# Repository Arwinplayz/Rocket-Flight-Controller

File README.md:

# Custom Flight Controller
A custom Flight Controller maded within kicad, specificaly for rockets.
---

## Project Overview
The goal was to create a custom Flight Controller which was capable of utilising TVC to guide a rocket.

---

## Screenshots

### 1. Overall

### 2. Schematic

### 3. PCB layout

### 4. Design

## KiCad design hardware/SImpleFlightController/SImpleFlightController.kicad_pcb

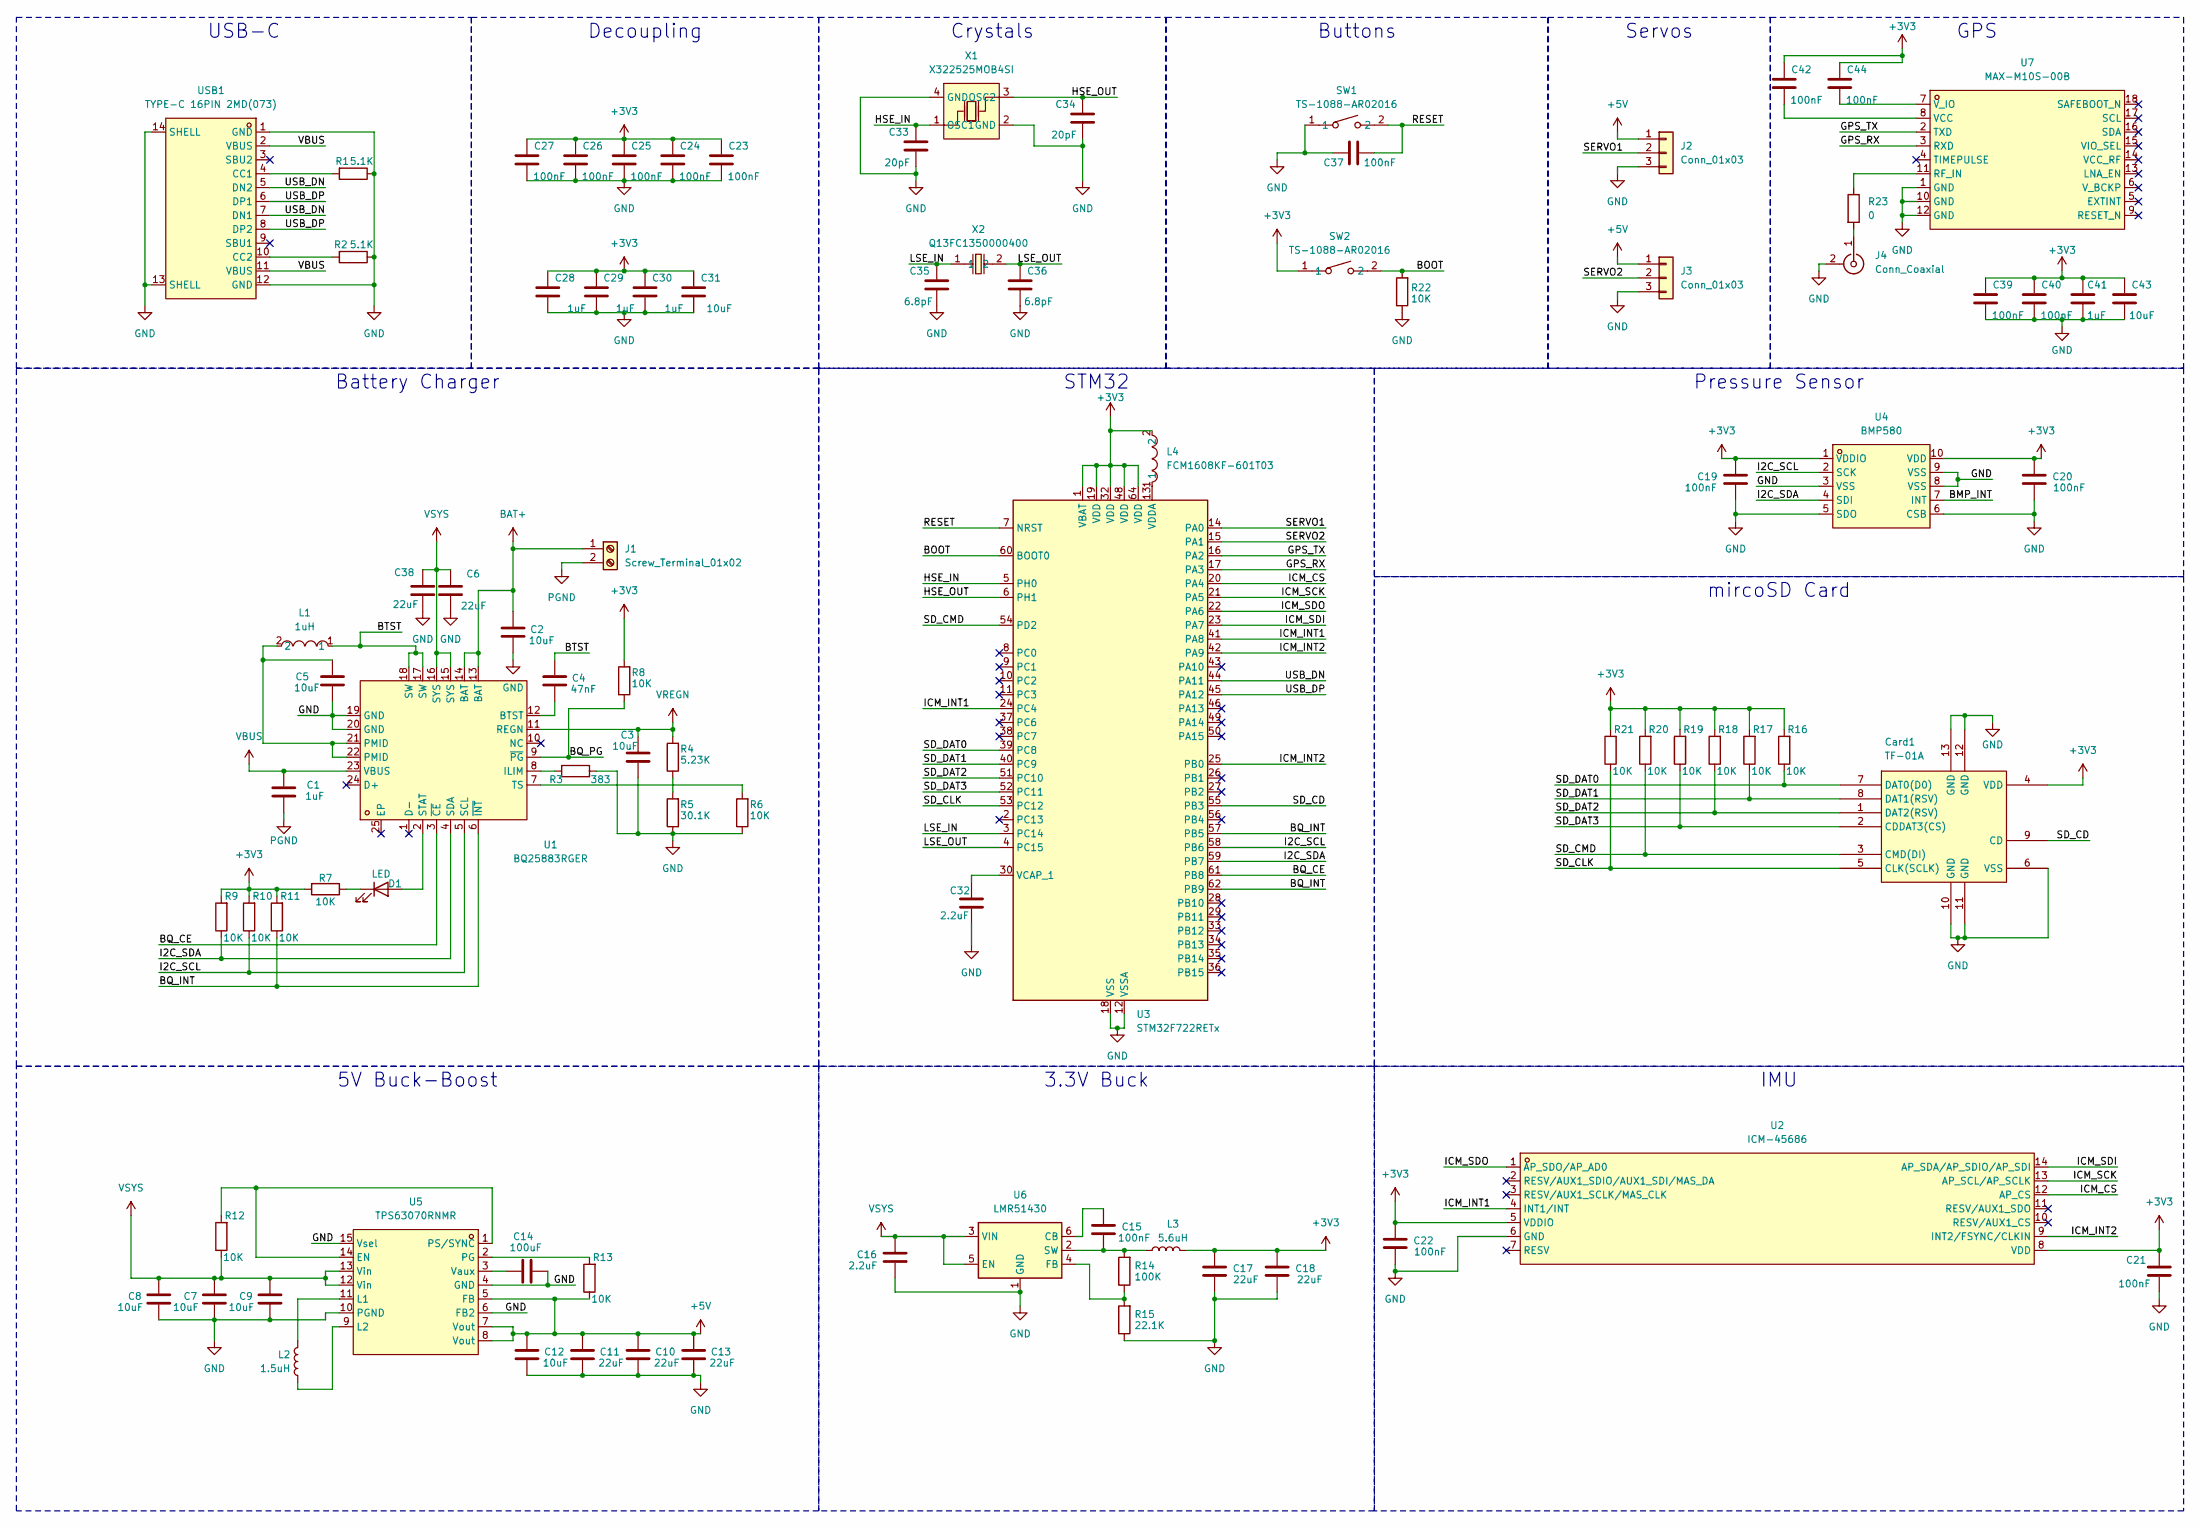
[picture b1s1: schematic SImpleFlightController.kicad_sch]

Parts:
C1, C28, C29, C30, C41: 1uF; C_0402_1005Metric
C2, C9, C12: 10uF; C_0603_1608Metric
C3, C5, C31, C43: 10uF; C_0402_1005Metric
C4: 47nF; C_0201_0603Metric
C6, C38: 22uF; C_0603_1608Metric
C7, C8: 10uF; C_0805_2012Metric
C10, C11, C13: 22uF; C_0805_2012Metric
C14: 100uF; C_0201_0603Metric
C15, C19, C20, C21, C22, C23, C24, C25, C26, C27, C37: 100nF; C_0201_0603Metric
C16: 2.2uF; C_0603_1608Metric
C17, C18: 22uF; C_0402_1005Metric
C32: 2.2uF; C_0201_0603Metric
C33, C34: 20pF; C_0201_0603Metric
C35, C36: 6.8pF; C_0201_0603Metric
C39, C40, C42, C44: 100nF; C_0402_1005Metric
Card1: TF-01A; TF-SMD_TF-01A; LCSC Part C91145
D1: LED; LED_0402_1005Metric
J1: Screw_Terminal_01x02; TerminalBlock_Xinya_XY308-2.54-2P_1x02_P2.54mm_Horizontal
J2, J3: Conn_01x03; PinHeader_1x03_P2.54mm_Vertical
J4: Conn_Coaxial; U.FL_Hirose_U.FL-R-SMT-1_Vertical
L1: 1uH; L2520; LCSC Part C435392
L2: 1.5uH; IND-SMD_L4.0-W4.0-A
L3: 5.6uH; IND-SMD_L3.0-W3.0
L4: FCM1608KF-601T03; L0603; LCSC Part C141723
R1, R2: 5.1K; R_0201_0603Metric
R3: 383; R_0201_0603Metric
R4: 5.23K; R_0201_0603Metric
R5: 30.1K; R_0201_0603Metric
R6, R7, R8, R9, R10, R11, R12, R13, R16, R17, R18, R19, R20, R21, R22: 10K; R_0201_0603Metric
R14: 100K; R_0402_1005Metric
R15: 22.1K; R_0402_1005Metric
R23: 0; R_0201_0603Metric
SW1, SW2: TS-1088-AR02016; SW-SMD_L3.9-W3.0-P4.45; LCSC Part C720477
U1: BQ25883RGER; VFQFPN-24_L4.0-W4.0-P0.50-BL-EP2.8; LCSC Part C544362
U2: ICM-45686; LGA-14_L3.0-W2.5-P0.50-TL; LCSC Part C22459454
U3: STM32F722RETx; LQFP-64_10x10mm_P0.5mm
U4: BMP580; LGA-10_L2.0-W2.0-P0.50-TL_BMP580; LCSC Part C22391138
U5: TPS63070RNMR; VQFN-HR-15_L3.0-W2.5-P0.50-BL_TPS63070RNMR; LCSC Part C109322
U6: LMR51430; SOT-23-6
U7: MAX-M10S-00B; SMD-18_L10.1-W9.7-P1.10-TL_SKG09F; LCSC Part C4153167
USB1: TYPE-C 16PIN 2MD(073); USB-C-SMD_TYPE-C-6PIN-2MD-073; LCSC Part C2765186
X1: X322525MOB4SI; CRYSTAL-SMD_4P-L3.2-W2.5-BL; LCSC Part C9006
X2: Q13FC1350000400; FC-135R_L3.2-W1.5; LCSC Part C32346

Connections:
+3V3: C17.1, C18.1, C19.1, C20.1, C21.1, C22.1, C23.1, C24.1, C25.1, C26.1, C27.1, C28.1, C29.1, C30.1, C31.1, C39.1, C40.1, C41.1, C42.1, C42.2, C43.1, C44.1, C44.2, Card1.4 (VDD), L3.2, L4.2, R7.2, R8.2, R9.2, R10.2, R11.2, R16.2, R17.2, R18.2, R19.2, R20.2, R21.2, SW2.1, U2.5 (VDDIO), U2.8 (VDD), U3.1 (VBAT), U3.19 (VDD), U3.32 (VDD), U3.48 (VDD), U3.64 (VDD), U4.1 (VDDIO), U4.10 (VDD), U7.7 (V_IO), U7.8 (VCC); also elsewhere on the board
+5V: C10.1, C11.1, C12.1, C13.1, J2.1, J3.1, R13.1, U5.5 (FB), U5.7 (Vout), U5.8 (Vout)
/BMP_INT: U4.7 (INT)
/BOOT: R22.2, SW2.2, U3.60 (BOOT0); also elsewhere on the board
/BQ_CE: U1.3 (~CE), U3.61 (PB8)
/BQ_INT: R11.1, U1.6 (~INT), U3.57 (PB5), U3.62 (PB9)
/BQ_PG: R8.1, U1.9 (~PG)
/BTST: C4.1, L1.1, U1.17 (SW), U1.18 (SW)
/GPS_RX: U3.17 (PA3), U7.3 (RXD)
/GPS_TX: U3.16 (PA2), U7.2 (TXD)
/HSE_IN: C33.1, U3.5 (PH0), X1.1 (OSC1)
/HSE_OUT: C34.1, U3.6 (PH1), X1.3 (OSC2)
/I2C_SCL: R10.1, U1.5 (SCL), U3.58 (PB6), U4.2 (SCK)
/I2C_SDA: R9.1, U1.4 (SDA), U3.59 (PB7), U4.4 (SDI)
/ICM_CS: U2.12 (AP_CS), U3.20 (PA4)
/ICM_INT1: U2.4 (INT1/INT), U3.24 (PC4), U3.41 (PA8)
/ICM_INT2: U2.9 (INT2/FSYNC/CLKIN), U3.25 (PB0), U3.42 (PA9)
/ICM_SCK: U2.13 (AP_SCL/AP_SCLK), U3.21 (PA5)
/ICM_SDI: U2.14 (AP_SDA/AP_SDIO/AP_SDI), U3.23 (PA7)
/ICM_SDO: U2.1 (AP_SDO/AP_AD0), U3.22 (PA6)
/LSE_IN: C35.1, U3.3 (PC14), X2.1
/LSE_OUT: C36.1, U3.4 (PC15), X2.2
/RESET: C37.2, SW1.2, U3.7 (NRST); also elsewhere on the board
/SD_CD: Card1.9 (CD), U3.55 (PB3)
/SD_CLK: Card1.5 (CLK(SCLK)), R21.1, U3.53 (PC12)
/SD_CMD: Card1.3 (CMD(DI)), R20.1, U3.54 (PD2)
/SD_DAT0: Card1.7 (DAT0(D0)), R16.1, U3.39 (PC8)
/SD_DAT1: Card1.8 (DAT1(RSV)), R17.1, U3.40 (PC9)
/SD_DAT2: Card1.1 (DAT2(RSV)), R18.1, U3.51 (PC10)
/SD_DAT3: Card1.2 (CDDAT3(CS)), R19.1, U3.52 (PC11)
/SERVO1: J2.2, U3.14 (PA0)
/SERVO2: J3.2, U3.15 (PA1)
/USB_DN: U3.44 (PA11), USB1.5 (DN2), USB1.7 (DN1)
/USB_DP: U3.45 (PA12), USB1.6 (DP1), USB1.8 (DP2)
BAT+: C2.1, J1.1, U1.13 (BAT), U1.14 (BAT)
GND: C2.2, C3.2, C5.2, C6.2, C7.2, C8.2, C9.2, C10.2, C11.2, C12.2, C13.2, C14.1, C16.2, C17.2, C18.2, C19.2, C20.2, C21.2, C22.2, C23.2, C24.2, C25.2, C26.2, C27.2, C28.2, C29.2, C30.2, C31.2, C32.2, C33.2, C34.2, C35.2, C36.2, C37.1, C38.2, C39.2, C40.2, C41.2, C43.2, Card1.6 (VSS), Card1.10 (GND), Card1.11 (GND), Card1.12 (GND), Card1.13 (GND), J2.3, J3.3, J4.2 (Ext), R1.1, R2.1, R3.1, R5.1, R6.1, R15.1, R22.1, SW1.1, U1.19 (GND), U1.20 (GND), U2.6 (GND), U3.12 (VSSA), U3.18 (VSS), U3.31 (VSS), U3.47 (VSS), U3.63 (VSS), U4.3 (VSS), U4.5 (SDO), U4.6 (CSB), U4.8 (VSS), U4.9 (VSS), U5.4 (GND), U5.6 (FB2), U5.10 (PGND), U5.15 (Vsel), U6.1 (GND), U7.1 (GND), U7.10 (GND), U7.12 (GND), USB1.1 (GND), USB1.12 (GND), USB1.13 (SHELL), USB1.14 (SHELL), X1.2 (GND), X1.4 (GND); also elsewhere on the board
unnamed: C5.1, L1.2, U1.21 (PMID), U1.22 (PMID)
unnamed: D1.2 (A), U1.2 (STAT)
unnamed: D1.1 (K), R7.1
unnamed: J4.1 (In), R23.2
unnamed: R4.1, R5.2
unnamed: C4.2, U1.12 (BTST)
unnamed: R3.2, U1.8 (ILIM)
unnamed: R6.2, U1.7 (TS)
unnamed: C32.1, U3.30 (VCAP_1)
unnamed: L4.1, U3.13 (VDDA)
unnamed: R12.2, U5.1 (PS/SYNC), U5.14 (EN)
unnamed: L2.1, U5.11 (L1)
unnamed: L2.2, U5.9 (L2)
unnamed: R13.2, U5.2 (PG)
unnamed: C14.2, U5.3 (Vaux)
unnamed: C15.1, U6.6 (CB)
unnamed: R14.1, R15.2, U6.4 (FB)
unnamed: C15.2, L3.1, R14.2, U6.2 (SW)
unnamed: R23.1, U7.11 (RF_IN)
unnamed: R1.2, USB1.4 (CC1)
unnamed: R2.2, USB1.10 (CC2)
PGND: C1.2, J1.2
VBUS: C1.1, U1.23 (VBUS), USB1.2 (VBUS), USB1.11 (VBUS)
VREGN: C3.1, R4.2, U1.11 (REGN)
VSYS: C6.1, C7.1, C8.1, C9.1, C16.1, C38.1, R12.1, U1.15 (SYS), U1.16 (SYS), U5.12 (Vin), U5.13 (Vin), U6.3 (VIN), U6.5 (EN)

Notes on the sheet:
Buttons
mircoSD Card
USB-C
Crystals
GPS
Servos
Battery Charger
STM32
IMU
5V Buck-Boost
Pressure Sensor
Decoupling
3.3V Buck

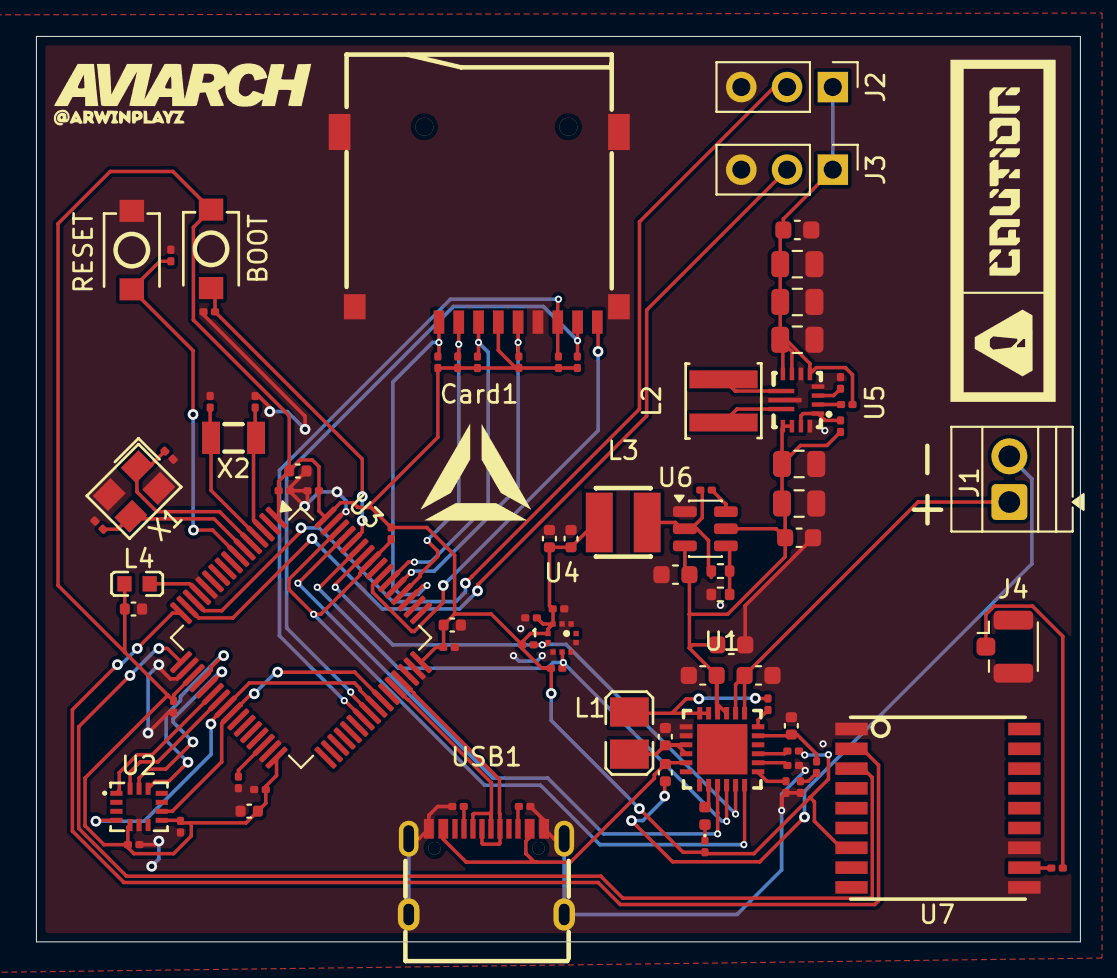
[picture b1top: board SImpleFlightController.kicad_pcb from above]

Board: 2 copper layers, 58.0 x 50.3 mm, 83 parts (0 on the bottom side), 60 nets.

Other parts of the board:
BOOT: TS-1088-AR02016; SW-SMD_L3.9-W3.0-P4.45
RESET: TS-1088-AR02016; SW-SMD_L3.9-W3.0-P4.45

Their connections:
+3V3: BOOT.1; also elsewhere on the board
/BOOT: BOOT.2; also elsewhere on the board
/RESET: RESET.2; also elsewhere on the board
GND: RESET.1; also elsewhere on the board

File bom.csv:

Designator,Footprint,Quantity,Value,LCSC Part #
"BOOT, RESET",SW-SMD_L3.9-W3.0-P4.45,2,TS-1088-AR02016,C720477
"C1, C28, C29, C30",0402,4,1uF,
"C10, C11, C13",0805,3,22uF,
"C12, C2, C9",0603,3,10uF,
C14,0201,1,100uF,
"C15, C19, C20, C21, C22, C23, C24, C25, C26, C27, C37",0201,11,100nF,
C16,0603,1,2.2uF,
"C17, C18",0402,2,22uF,
"C3, C31, C5",0402,3,10uF,
C32,0201,1,2.2uF,
"C33, C34",0201,2,20pF,
"C35, C36",0201,2,6.8pF,
"C38, C6",0603,2,22uF,
C4,0201,1,47nF,
"C7, C8",0805,2,10uF,
CARD1,TF-SMD_TF-01A,1,TF-01A,C91145
D1,0402,1,LED,
J1,TerminalBlock_Xinya_XY308-2.54-2P_1x02_P2.54mm_Horizontal,1,Screw_Terminal_01x02,
"J2, J3",PinHeader_1x03_P2.54mm_Vertical,2,Conn_01x03,
J4,U.FL_Hirose_U.FL-R-SMT-1_Vertical,1,Conn_Coaxial,
L1,L2520,1,1uH,C435392
L2,IND-SMD_L4.0-W4.0-A,1,1.5uH,
L3,IND-SMD_L3.0-W3.0,1,5.6uH,
L4,L0603,1,FCM1608KF-601T03,C141723
"R1, R2",0201,2,5.1K,
"R10, R11, R12, R13, R16, R17, R18, R19, R20, R21, R22, R6, R7, R8, R9",0201,15,10K,
R14,0402,1,100K,
R15,0402,1,22.1K,
R23,0201,1,0,
R3,0201,1,383,
R4,0201,1,5.23K,
R5,0201,1,30.1K,
U1,VFQFPN-24_L4.0-W4.0-P0.50-BL-EP2.8,1,BQ25883RGER,C544362
U2,LGA-14_L3.0-W2.5-P0.50-TL,1,ICM-45686,C22459454
U3,LQFP-64_10x10mm_P0.5mm,1,STM32F722RETx,
U4,LGA-10_L2.0-W2.0-P0.50-TL_BMP580,1,BMP580,C22391138
U5,VQFN-HR-15_L3.0-W2.5-P0.50-BL_TPS63070RNMR,1,TPS63070RNMR,C109322
U6,SOT-23-6,1,LMR51430,
U7,SMD-18_L10.1-W9.7-P1.10-TL_SKG09F,1,MAX-M10S-00B,C4153167
USB1,USB-C-SMD_TYPE-C-6PIN-2MD-073,1,TYPE-C 16PIN 2MD(073),C2765186
X1,CRYSTAL-SMD_4P-L3.2-W2.5-BL,1,X322525MOB4SI,C9006
X2,FC-135R_L3.2-W1.5,1,Q13FC1350000400,C32346

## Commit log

2025-12-20 added local files
2025-12-24 updated schematics
2026-02-17 updated GPS to front
2026-02-17 added photos
